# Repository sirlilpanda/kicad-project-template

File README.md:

# kicad project template

a cool table showing the workflow of all the kicad projects.
| project_name | DRC | ERC |
| ------------ | --- | --- |
| template | [❌](https://github.com/sirlilpanda/kicad-project-template/actions/runs/14507154830/attempts/1#summary-40698563204)| [✅](https://github.com/sirlilpanda/kicad-project-template/actions/runs/14507154830/attempts/1#summary-40698563199) | 

for a quick guide check [project setup](#project-setup)

This is a simple project template for new kicad projects. This template has some basic setup already completed such as workflows for auto creating all the things you forget when creating a kicad project such as:

- [gerbers](https://github.com/sirlilpanda/kicad-project-template/tree/main/template_gerber.zip)
- [bom](https://github.com/sirlilpanda/kicad-project-template/tree/main/template_bom_report.md)
- [schematic pdf](https://github.com/sirlilpanda/kicad-project-template/tree/main/template_schematic.pdf)

This workflow will also run the design rules check on the PCB and schematic to ensure that you upload a working PCB. These reports are uploaded as summaries within the github [actions tab](https://github.com/sirlilpanda/kicad-project-template/actions/runs/14507154830). This template has a simple schematic PCB in it (because DRC fails on an empty PCB). Shown below is the example PCB.

besides from that the project also has:

- common predefined trace widths
- smallest vias size [JLCPBC allows](https://jlcpcb.com/capabilities/Capabilities#Drilling)
- custom net colours in the schematic editor
    - `red` for +V
    - `blue` for -V
    - `grey` for ground

to create a repo from this template follow this [guide](https://docs.github.com/en/repositories/creating-and-managing-repositories/creating-a-repository-from-a-template)

contained in this template are:
---
- `.github/` : all files relating to github actions and other admin see [here](https://docs.github.com/en/communities/setting-up-your-project-for-healthy-contributions) for more example of what can be placed in it
    - `report_processing` : where the python scripts are stored for processing the json report data from kicad
    - `report_templates` : where the template for said reports are stored
    - `workflows/` : this is where the github actions are kept
        - `main.yaml` : the main github action that will auto generate all files required and run DRC and ERC
    - `rename.py` : the script for renaming the project
- `hardware/` : this is where the kicad projects live note this can be changed
- `docs/` : this is where the generate docs are placed by default
    - `BOM/`     : where the bill of materials and price breakdown are kept
        - `bill_of_materials.csv`: the auto generated bom for the kicad project
        - `bom_report.md` : a report for the bill of materials
    - `template_schematic.pdf` : the schematic for the kicad project, auto generated by the github action
- `pcbs/` : this is where the auto generated gerbers for the kicad project are stored

- `res/` : where resources are stored for the README

- `.gitignore`: a slightly modified gitignore from the [standard one](https://github.com/github/gitignore/blob/main/KiCad.gitignore)

- `project_settings.yaml` : where the settings for this project is stored

- `README.md` : this file, suggest you change this one creating your project

## project settings
there are currently very few project settings that can be changed (will will be change in the future) these are:
| setting                     | description                                                       |
| --------------------------- | ----------------------------------------------------------------- |
| has_been_set_up             | a flag to tell the setup action if the project has been set up    |
| project_name                | the name of the project, this will be set to the name of the repo |
| production_formats          | the output production format for the PCBs                         |
| dynamic_read_me             | allow the readme to be updated using the given template           |
| bom_template_path           | the template used to write the bom report files                   |
| erc_report_template_path    | the template used to write the erc report files                   |
| drc_report_template_path    | the template used to write the drc report files                   |
| readme_template_path        | the template used to write projects readme                        |
| schematic_output_name       | the name suffix of the generated schematics                       |
| bom_csv_output_name         | the name suffix of the generated bom csv file                     |
| bom_report_output_name      | the name suffix of the generated bom report                       |
| production_file_output_name | the name suffix of the generated production file                  |
| schematic_output_path       | the output path of the generated schematics files                 |
| bom_csv_output_path         | the output path of the generated bom csv file                     |
| bom_report_output_path      | the output path of the generated bom report                       |
| production_file_output_path | the output path of the generated production file                  |

## project setup

### creating a new repo with the template

creating a new template from a repo is simple:

1. click on the button in the top right hand corner called `use this template`

2. when the drop down menu appears click on `create a new repository`

3. once you click you will be brought to this page, note that the repo name you choose here will be the name that you kicad project is called.

after these steps you then need to configure the repo settings to do their magic see [configuring repo settings](#configuring-repo-settings) for what to do next.

### configuring repo settings

once you have created a new repo with the template, you ill have to configure the github action settings. this is because you will get an error that looks something along these lines:

where the action can not commit the changes due to not having permissions follow these steps:
1. open the repo setting

2. then head in to actions : General

3. then scroll down to workflow permissions and ensure that both
    `Read and write permissions` and `Allow GitHub Actions to create and approve pull requests` are ticked as seen below

this should fix the problem if not, go harass stack overflow they need it
Once all of these steps have been followed the workflow should be passing, however the `README.md` will only update on the next push request.

## editing the readme

As this repo can and will automatically update the repo corresponding to the given readme template. If you dont want to use this you can always disable this by setting the `dynamic_read_me` to `false`. but if you want some very cool features like auto updating tables to show what projects are passing the rules check or simple links to parts of your directory. then have a look at the template readme and learn [mustache](https://mustache.github.io/)

## improvements

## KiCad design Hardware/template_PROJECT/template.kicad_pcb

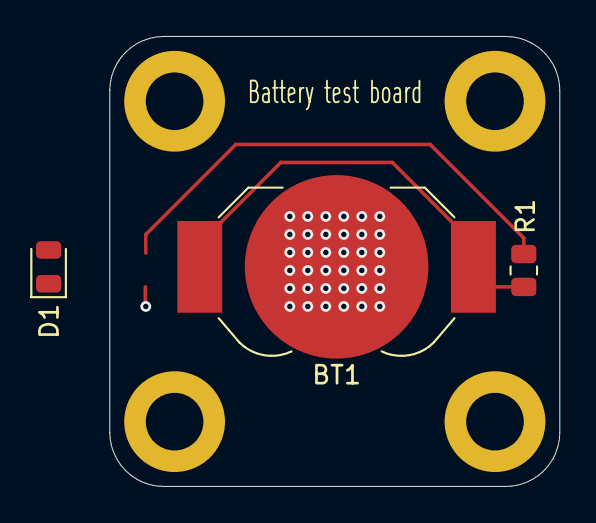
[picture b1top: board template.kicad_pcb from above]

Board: 4 copper layers, 25.0 x 25.0 mm, 7 parts (0 on the bottom side), 3 nets.

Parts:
BT1: Battery; BatteryHolder_LINX_BAT-HLD-012-SMT
D1: LED; LED_0805_2012Metric
H1, H2, H3, H4: MountingHole; MountingHole_3.2mm_M3_DIN965_Pad
R1: R; R_0805_2012Metric

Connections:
/+V: BT1.1 (+), R1.1
/-V: BT1.2 (-), D1.1 (K)
unnamed: D1.2 (A), R1.2

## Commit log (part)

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2024-11-01 auto updated doc
2024-11-01 erc and drc should now pass
2024-11-01 added template
2024-11-01 now processes bom csv to markdown reports
2024-11-01 added bom creating to the workflow
2024-11-01 fix date string
2024-11-01 script for renaming the project
2024-11-01 added pathlib and ruamel.yaml
2024-11-01 settings for the project
2024-11-01 created setup workflow
2024-11-01 no longer needed
2024-11-01 see if this stop trying to setup in the template repo
2024-11-01 is it here
2024-11-01 removed the dot
2024-11-01 renamed
2024-11-01 i forgot to checkout the repo
2024-11-01 why is there no files in here
2024-11-01 should be in the right spot now
2024-11-01 removing prints because ruamel.yaml is bad
2024-11-01 set the project name
2024-11-01 will printing to standard errror work
2024-11-01 whats going on here
2024-11-01 now saves to a file
2024-11-01 auto updated
2024-11-01 now no longer depends on project name
2024-11-01 added more comments
2024-11-01 added extra comments
2024-11-01 added documention
2024-11-01 new images for the readme
2024-11-02 Breakout KiCAD environment setup into composite action
2024-11-02 Share KiCAD setup dependency between jobs
2024-11-02 Breakout ERC/DRC reporting into own workflow
2024-11-02 Correct use case in report push job
2024-11-02 Add missing test job metadata
2024-11-02 Correct output passing in KiCAD setup workflow
2024-11-02 Tweak formatting of kicad setup outputs
2024-11-02 Attempt directly passing outputs through setup
2024-11-02 Double down on passing outputs directly
2024-11-08 Attempt correction of settings syntax, to revert to composite action if fails
2024-11-08 Revert to a composite workflow approach
2024-11-08 Run checkout before KiCAD setup
2024-11-08 Mark kicad_setup.yaml as executable to fix permissions issues
2024-11-08 Tweak outputs syntax per github complaints
2024-11-08 Use "uses" instead of "run" - Github docs not very clear on which is correct
2024-11-08 Move KiCAD setup into own directory per github complaints?
2024-11-08 Add shell spec to step, again not really well documented
2024-11-08 Back to fighting "unexpected mapping"
2024-11-11 decoupled workflow for DRC
2024-11-11 decoupled workflow for ERC
2024-11-11 workflow for all normal production files
2024-11-11 commeted out the kicad work flow as all of it has been move to differnt repos
2024-11-11 i cant read docs
2024-11-11 production files
2024-11-11 should now force push
2024-11-11 should now force push maybe if im lucky
2024-11-11 pulls before push now so it should work
2024-11-11 maybe this will work now
2024-11-11 combined workflows again
2024-11-11 updated move paths
2024-11-11 forgot a slash
2024-11-11 new setting in project settings
2024-11-11 starting to test matrixes for multiple kicad projects
2024-11-11 fixed name
2024-11-11 commiting now also depends on matrix setup
2024-11-11 if there are no extra kicad project setting should be null now
2024-11-11 should only add the files i want to upload and not the other ones
2024-11-11 see what this outputs
2024-11-12 change list decal
2024-11-12 maybe it wants it as strings
2024-11-12 now using a python script for parseing the porject setting in the setup rather than the action, since it breaks on lists
2024-11-12 script for getting all the kicad projects name out of the settings
2024-11-12 classic windows blunder
2024-11-12 fixed paths
2024-11-12 changed output slightly so i dont have to do more scripting in bash
2024-11-12 commented out the push for the moment
2024-11-12 will the matrix work
2024-11-12 lets hope this yaml parser works
2024-11-12 removed the qoute marks
2024-11-12 all jobs use the new yaml parser
2024-11-12 fixed error squiggles
2024-11-12 checking to see what happends is sub pcbs are null
2024-11-12 now doesnt die when sub project names are null
2024-11-12 added actual project to the path
2024-11-12 not me forgetting how to write yaml
2024-11-12 remaned power board project for testing
2024-11-12 should move all the production files in to the last step
2024-11-12 move commnad should now throw everthing in correctly
2024-11-12 should now handle multiple erc
2024-11-12 fixed path
2024-11-12 all produciton files should now upload too
2024-11-12 re-enabled the pushing
2024-11-12 fixed download pattern
2024-11-12 should now cancel workflows if a new push cget commited
2024-11-12 now creates bom reports as well
2024-11-12 should now add the bom reports
2024-11-12 cleaned up files
2024-11-12 readded the dirs
2024-11-12 removed the gitkeeps
2024-11-12 removed the second project for merging in to main
2024-11-12 removed the second project
2024-11-12 updated to reflect new feature
2024-11-12 Update README.md
    fix grammer error
2024-11-12 updated names
2024-11-12 seeing if i can add the report hash for mustache in to the header of the md file
2024-11-12 maybe github wont complain if i do this
2024-11-12 sadly i cant make this hidden therefor it will stay in another file
2024-11-16 erc and drc reports should now upload as a step summnary rather than in to the repo
2024-11-16 added new project for testing
2024-11-16 now accpets a project name to use in templates
2024-11-16 added project name to the title
2024-11-16 now accpets the project name to use for the reports
2024-11-16 sadly has to be on one line
2024-11-16 should now create iboms
2024-11-16 should now create and upload the iboms
2024-11-16 just upload evertthing
2024-11-16 removed the ibom stuff and moving that to a new branch
2024-11-16 removed second project and cleaned up unused files
2024-11-16 spelling mistakes
2024-11-16 fixed workflow, now no longer move reports
2024-11-16 fixed spelling mistakes
2024-11-16 reports should now be shorter when no errors occured
2024-11-16 creating errors to check
2024-11-16 worked
2024-11-16 reports should now have nice linking to their sections
2024-11-16 removed erc and drc from being commited in the last step
2024-11-16 make it fail
2024-11-16 shouldnt fail now
2024-11-16 added some emojis because this needed some colour
2024-11-16 some one needs to take these away from me
2024-11-16 added some commments
2024-11-16 i need this in main to test the templates nicely
2024-11-16 maybe this will work
2024-11-17 changed to needs_setup
2024-11-17 setup action should now work
2024-11-17 moved to common location
2024-11-17 start of auto updating readme
2024-11-17 fixed syntax
2024-11-17 added project link
2024-11-17 renamed for a more consistent naming scheme
2024-11-17 time to see if upload artifact is a good workaround
2024-11-17 readme report template
2024-11-17 added more info to the drc and erc reports, also stops pushing to the repo for the moment
2024-11-17 added another project for action testing
2024-11-17 forgot to add the other project
2024-11-17 wrong syntax
2024-11-17 fixed drc report creation looking in wrong dir for json
2024-11-17 changed from .output to json
2024-11-17 poking around
2024-11-17 now has a link to the summary output of the action
2024-11-17 fixed qoutaion marks
2024-11-17 should now have all the infomation needed for the readme hash
2024-11-17 added readme template path and a dynamic read me setting
2024-11-17 added new report template sechema
2024-11-17 python script that is going to be used for processing all the output reports
2024-11-17 links should be fixed now
2024-11-17 should print out every args that the python script recivces
2024-11-17 will now print out all args
2024-11-17 testing to see if all output files are loaded correctly
2024-11-17 check to see if hash gets constructed correctly
2024-11-17 some more debugging
2024-11-17 i got board and added more emojis
2024-11-17 fixed extra json
2024-11-17 fixed script looking for artifact files in the wrong spot
2024-11-17 extras is now loaded correctly
2024-11-17 now uses the correct project list
2024-11-17 now longer added projects multiple times
2024-11-17 fixed erc saying drc_passing
2024-11-17 will now upload the new readme
2024-11-17 report hash now complete
2024-11-17 now pushes back in to the repo
2024-11-17 download readme is no longer looking for a pattern
2024-11-17 listing is now always so i can debug faster
2024-11-17 maybe new readme already overwrite things
2024-11-17 clean workflow structure slightly
2024-11-17 more links
2024-11-17 badge should now be branch indapendnt
2024-11-17 readme should no longer update when the setting in project_settings is set to false
2024-11-17 fixed broken link
2024-11-17 updated name scheme
2024-11-17 added some more docs
2024-11-17 make em fail
2024-11-17 instead of false its now null
2024-11-17 added more info to this
2024-11-17 updated schemas
2024-11-17 pass/fail emojis are now defineded within the python script
2024-11-17 correct the value
2024-11-17 removed the cancel checks to ensure they run everytime
2024-11-17 adding some extra debugging info
2024-11-17 i hate bools as strings
2024-11-17 removed second project
2024-11-17 should always create reports
2024-11-17 moved hash schemas to the top of the template files in a comment
2024-11-17 no longer errors
2024-11-17 fixed the title slightly
2025-02-25 need to rerun workflows
2025-02-25 finding all kicad project now using find instead of a script
2025-02-25 fixed find command to actually find the files and not the testing command
2025-02-25 forgot what this command outputed
2025-02-25 trying new find command
2025-02-25 suffering with multi line input
2025-02-25 added another project for testing
2025-02-25 checking what im creating
2025-02-25 quotes
2025-02-25 wrong command
2025-02-25 removed newlines
2025-02-25 what am i passing to output
2025-02-25 testing
2025-02-26 removing trailing comma
2025-02-26 forgot to have id for step output
2025-02-26 readding rest of steps to check names
2025-02-26 i know this doesnt work just checking its mostly working sofar
2025-02-26 created new project settings
2025-02-26 moved docs and pcb in to root dir
2025-02-26 removed erc and production file for the moment
2025-02-26 setting project name as an env
2025-02-26 why is this failing
2025-02-26 added comment
2025-02-26 should fail now
2025-02-26 erc should now output something
2025-02-26 should work now
2025-02-26 checking to see if these envs work
2025-02-26 need to split this in to 2 steps
2025-02-26 checking creating production files works
2025-02-26 should now push back in to the repo
2025-02-26 dubug print
2025-02-26 fixed dicts not correctly merging
2025-02-26 fixing paths
2025-02-26 added the ablity to have custom file names
2025-02-26 should now allow for custom output file names
2025-02-26 cleaned
2025-02-26 need a gitkeep for the moment
2025-02-26 added gitkeep
2025-02-26 removed sub project as no longer needed, may add back if an ignore list is desired
2025-02-26 fixed typo
2025-02-27 fixed bad merge
2025-04-17 version bump
